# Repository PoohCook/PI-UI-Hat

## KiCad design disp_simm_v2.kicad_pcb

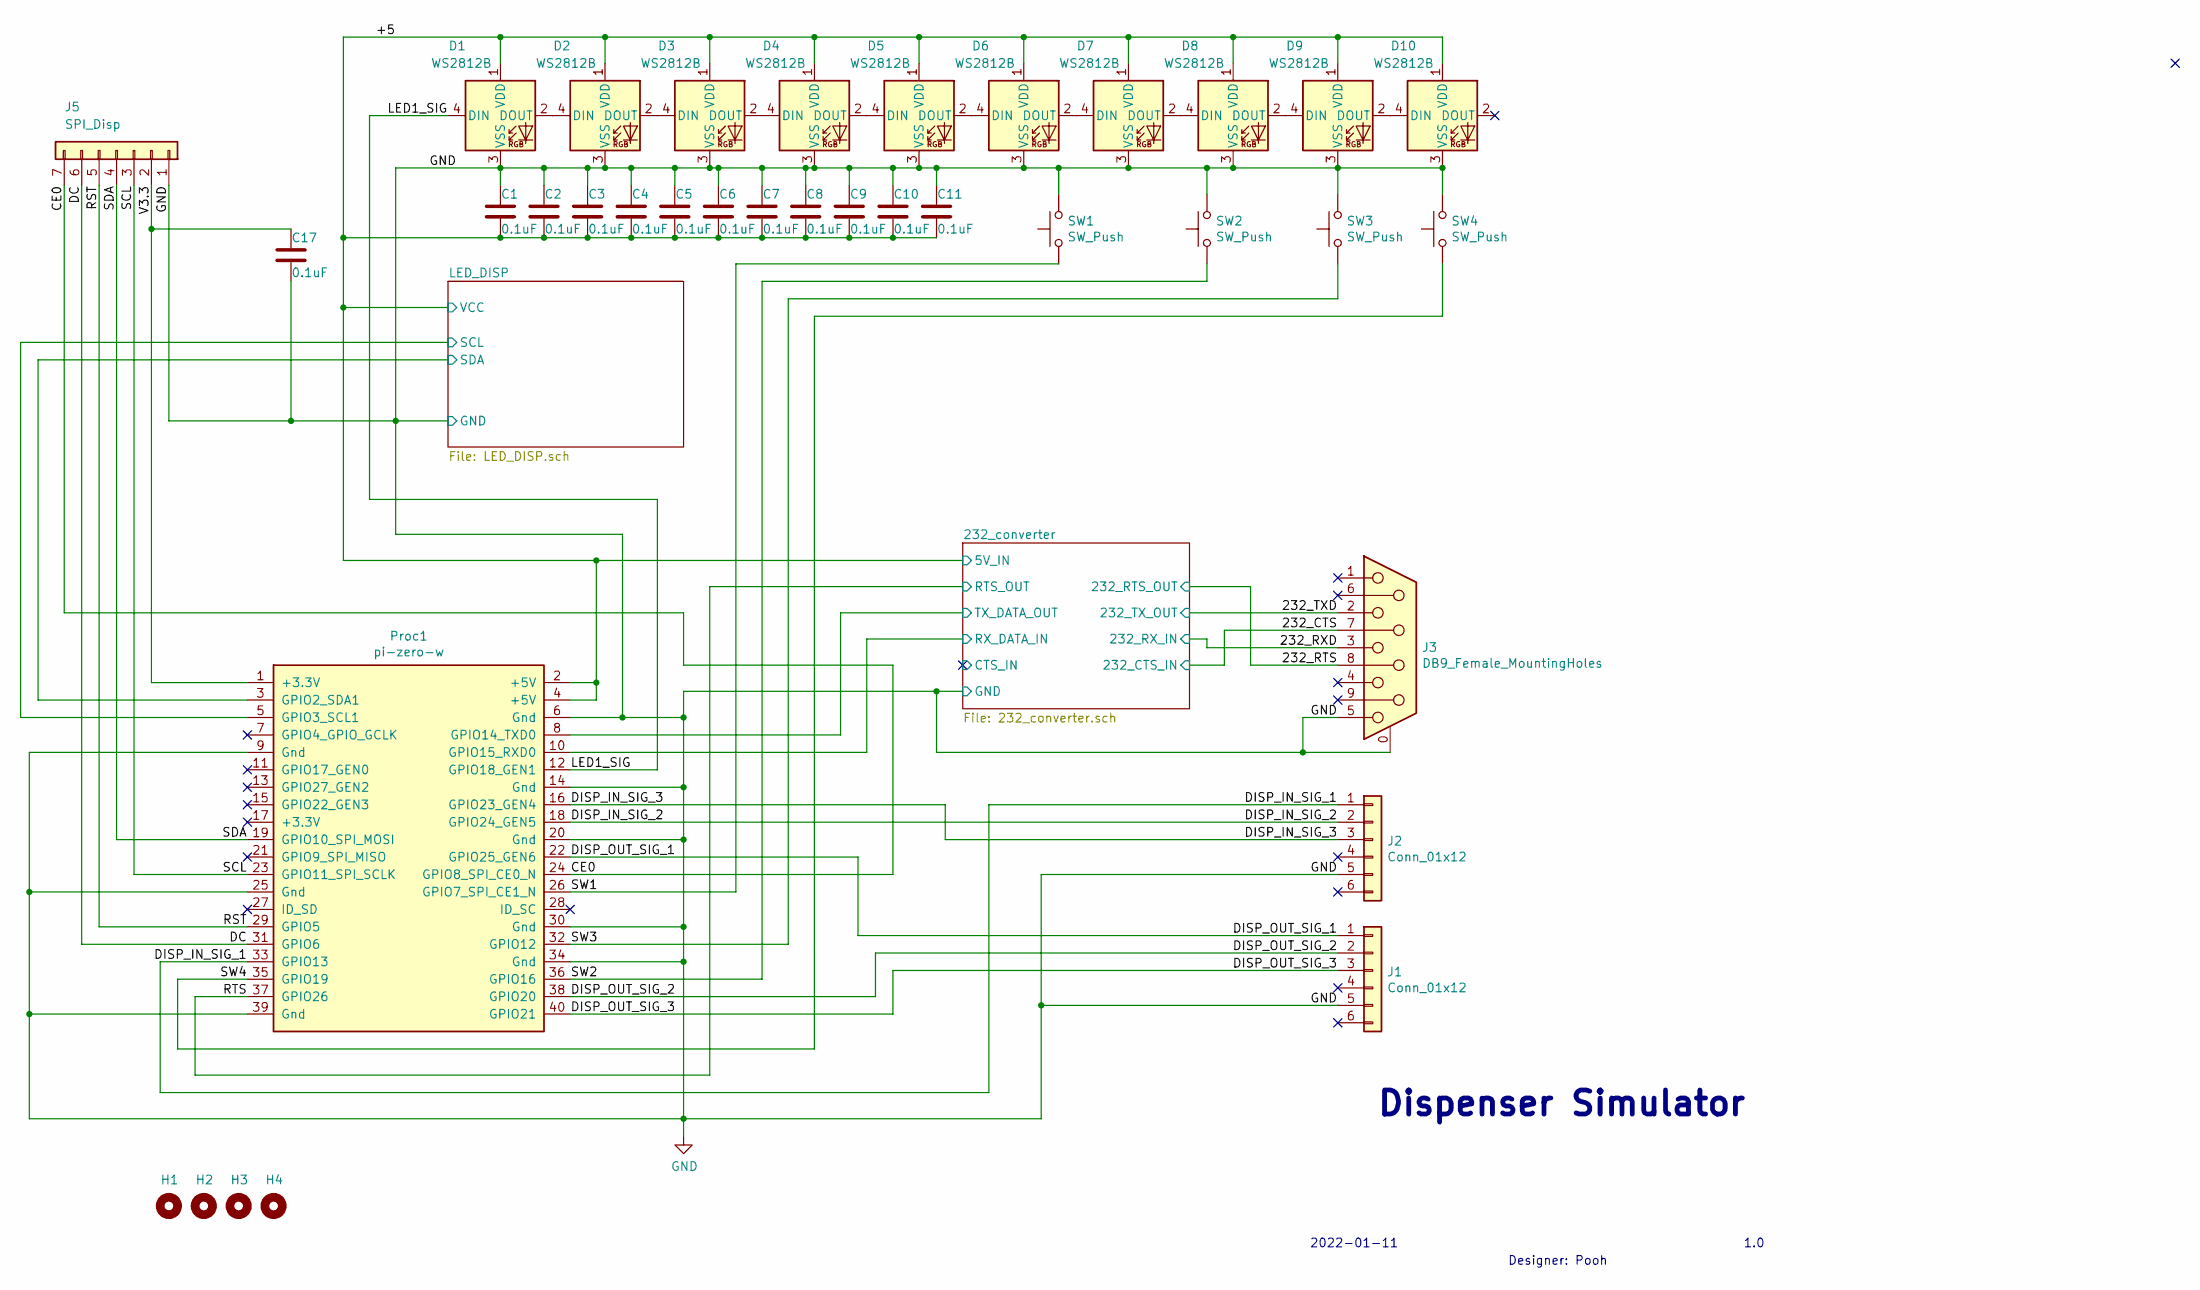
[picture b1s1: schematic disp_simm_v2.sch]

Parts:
C1, C2, C3, C4, C5, C6, C7, C8, C9, C10, C11, C17: 0.1uF; C_0805_2012Metric_Pad1.15x1.40mm_HandSolder; LCSC Part Number C49678
D1, D2, D3, D4, D5, D6, D7, D8, D9, D10: WS2812B; LED_WS2812B_PLCC4_5.0x5.0mm_P3.2mm; LCSC Part Number C2761795
H1, H2, H3, H4: MountingHole; MountingHole_2.5mm_Pad
J1, J2: Conn_01x12; JST-S06B-XASK-1
J3: DB9_Female_MountingHoles; DSUB-9_Female_Horizontal_P2.77x2.84mm_EdgePinOffset9.90mm_H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
J5: SPI_Disp; PinHeader_1x07_P2.54mm_Vertical
Proc1: pi-zero-w; pi-zero
SW1, SW2, SW3, SW4: SW_Push; SWA

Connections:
/232_CTS: J3.7; also elsewhere on the board
/232_RTS: J3.8; also elsewhere on the board
/232_RXD: J3.3; also elsewhere on the board
/232_TXD: J3.2; also elsewhere on the board
/232_converter/RX_DATA_IN: Proc1.10 (GPIO15_RXD0); also elsewhere on the board
/232_converter/TX_DATA_OUT: Proc1.8 (GPIO14_TXD0); also elsewhere on the board
/+5: C1.2, C2.2, C3.2, C4.2, C5.2, C6.2, C7.2, C8.2, C9.2, C10.2, C11.2, D1.1 (VDD), D2.1 (VDD), D3.1 (VDD), D4.1 (VDD), D5.1 (VDD), D6.1 (VDD), D7.1 (VDD), D8.1 (VDD), D9.1 (VDD), D10.1 (VDD), Proc1.2 (+5V), Proc1.4 (+5V); also elsewhere on the board
/CE0: J5.7, Proc1.24 (GPIO8_SPI_CE0_N)
/DC: J5.6, Proc1.31 (GPIO6)
/DISP_IN_SIG_1: J2.1, Proc1.33 (GPIO13)
/DISP_IN_SIG_2: J2.2, Proc1.18 (GPIO24_GEN5)
/DISP_IN_SIG_3: J2.3, Proc1.16 (GPIO23_GEN4)
/DISP_OUT_SIG_1: J1.1, Proc1.22 (GPIO25_GEN6)
/DISP_OUT_SIG_2: J1.2, Proc1.38 (GPIO20)
/DISP_OUT_SIG_3: J1.3, Proc1.40 (GPIO21)
/LED1_SIG: D1.4 (DIN), Proc1.12 (GPIO18_GEN1)
/LED_DISP/SCL: Proc1.5 (GPIO3_SCL1); also elsewhere on the board
/LED_DISP/SDA: Proc1.3 (GPIO2_SDA1); also elsewhere on the board
/RST: J5.5, Proc1.29 (GPIO5)
/RTS: Proc1.37 (GPIO26); also elsewhere on the board
/SCL: J5.3, Proc1.23 (GPIO11_SPI_SCLK)
/SDA: J5.4, Proc1.19 (GPIO10_SPI_MOSI)
/SW1: Proc1.26 (GPIO7_SPI_CE1_N), SW1.1
/SW2: Proc1.36 (GPIO16), SW2.1
/SW3: Proc1.32 (GPIO12), SW3.1
/SW4: Proc1.35 (GPIO19), SW4.1
/V3.3: C17.1, J5.2, Proc1.1 (+3.3V)
GND: C1.1, C2.1, C3.1, C4.1, C5.1, C6.1, C7.1, C8.1, C9.1, C10.1, C11.1, C17.2, D1.3 (VSS), D2.3 (VSS), D3.3 (VSS), D4.3 (VSS), D5.3 (VSS), D6.3 (VSS), D7.3 (VSS), D8.3 (VSS), D9.3 (VSS), D10.3 (VSS), J1.5, J2.5, J3.0 (PAD), J3.5, J5.1, Proc1.6 (Gnd), Proc1.9 (Gnd), Proc1.14 (Gnd), Proc1.20 (Gnd), Proc1.25 (Gnd), Proc1.30 (Gnd), Proc1.34 (Gnd), Proc1.39 (Gnd), SW1.2, SW2.2, SW3.2, SW4.2; also elsewhere on the board
unnamed: D1.2 (DOUT), D2.4 (DIN)
unnamed: D2.2 (DOUT), D3.4 (DIN)
unnamed: D3.2 (DOUT), D4.4 (DIN)
unnamed: D4.2 (DOUT), D5.4 (DIN)
unnamed: D5.2 (DOUT), D6.4 (DIN)
unnamed: D6.2 (DOUT), D7.4 (DIN)
unnamed: D7.2 (DOUT), D8.4 (DIN)
unnamed: D8.2 (DOUT), D9.4 (DIN)
unnamed: D9.2 (DOUT), D10.4 (DIN)

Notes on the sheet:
Dispenser Simulator
2022-01-11
1.0
Designer: Pooh

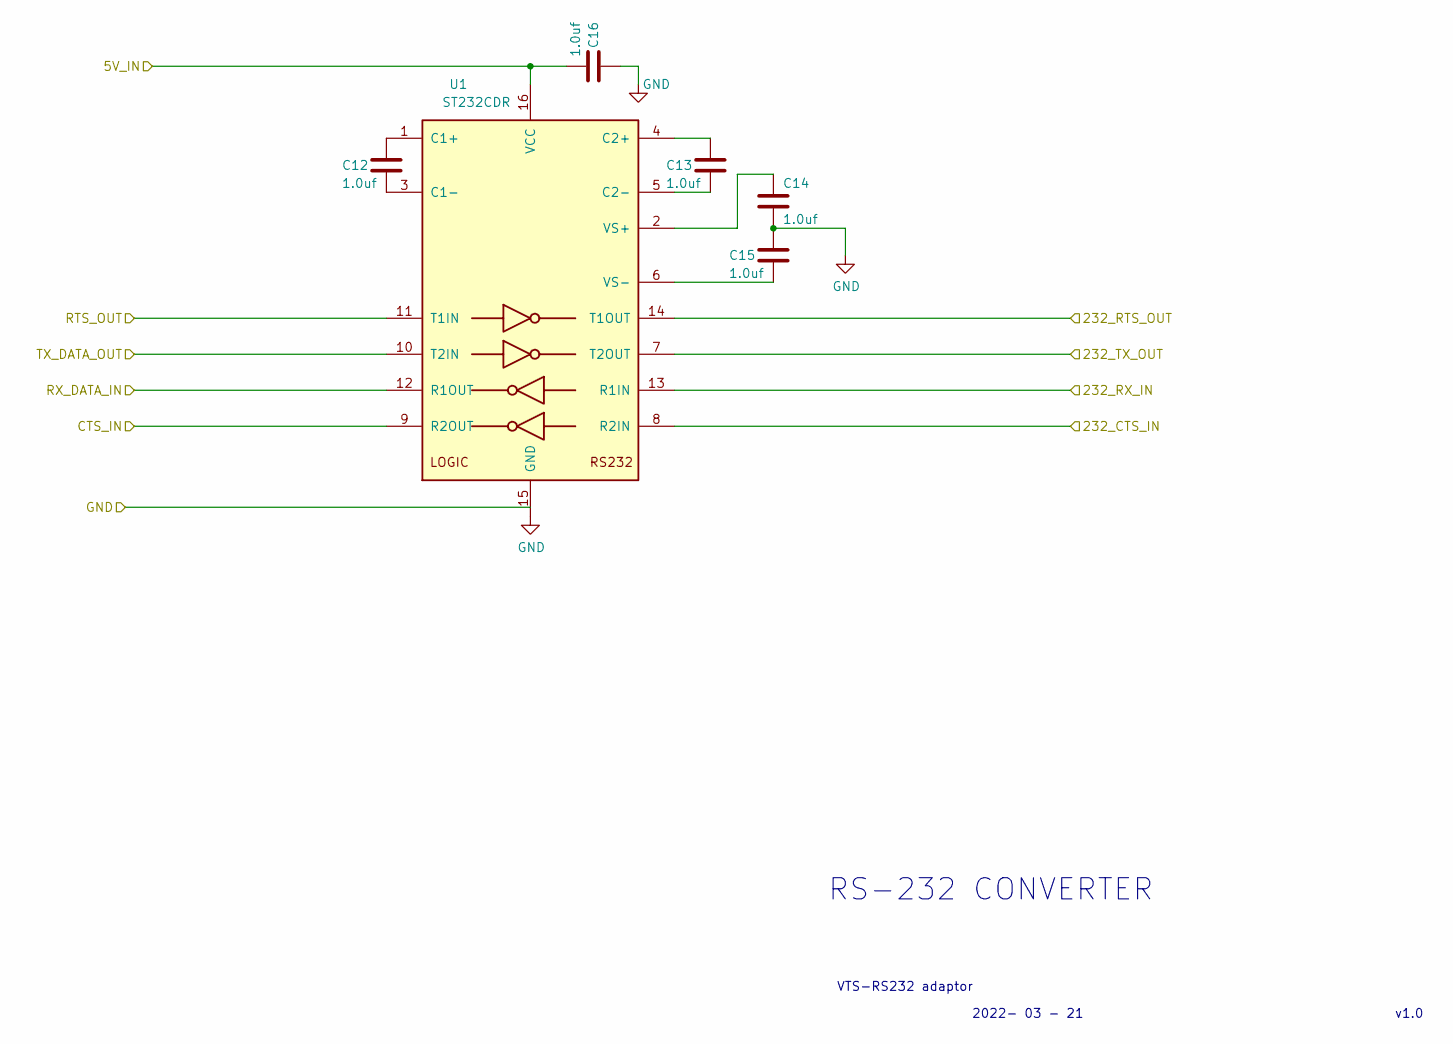
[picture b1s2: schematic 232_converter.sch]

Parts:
C12, C13, C14, C15, C16: 1.0uf; C_0805_2012Metric_Pad1.15x1.40mm_HandSolder; PartNum CL21B105KBFNNNE; LCSC Part Number C28323
U1: ST232CDR; SOIC-16_3.9x9.9mm_P1.27mm; PartNum ST232CDR; LCSC Part Number C6869

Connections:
/232_CTS: U1.8 (R2IN); also elsewhere on the board
/232_RTS: U1.14 (T1OUT); also elsewhere on the board
/232_RXD: U1.13 (R1IN); also elsewhere on the board
/232_TXD: U1.7 (T2OUT); also elsewhere on the board
/232_converter/CTS_IN: U1.9 (R2OUT)
/232_converter/RX_DATA_IN: U1.12 (R1OUT); also elsewhere on the board
/232_converter/TX_DATA_OUT: U1.10 (T2IN); also elsewhere on the board
/+5: C16.2, U1.16 (VCC); also elsewhere on the board
/RTS: U1.11 (T1IN); also elsewhere on the board
GND: C14.2, C15.1, C16.1, U1.15 (GND); also elsewhere on the board
unnamed: C12.1, U1.1 (C1+)
unnamed: C12.2, U1.3 (C1-)
unnamed: C13.1, U1.4 (C2+)
unnamed: C13.2, U1.5 (C2-)
unnamed: C14.1, U1.2 (VS+)
unnamed: C15.2, U1.6 (VS-)

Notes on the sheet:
RS-232 CONVERTER
VTS-RS232 adaptor
v1.0
2022- 03 - 21

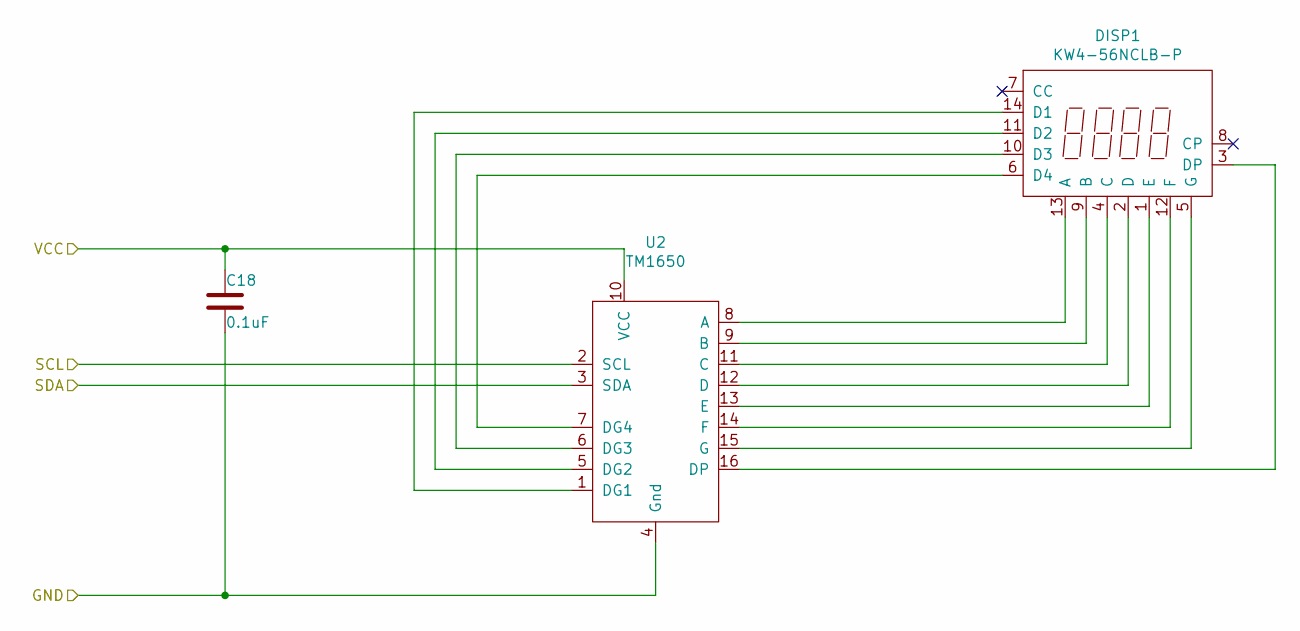
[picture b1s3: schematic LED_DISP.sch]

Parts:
C18: 0.1uF; C_0805_2012Metric_Pad1.15x1.40mm_HandSolder; LCSC Part Number C49678
DISP1: KW4-56NCLB-P; DIP-14_W15.24mm-Disp
U2: TM1650; SOP-16_4.55x10.3mm_P1.27mm; LCSC Part Number C44444

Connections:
/+5: C18.1, U2.10 (VCC); also elsewhere on the board
/LED_DISP/SCL: U2.2 (SCL); also elsewhere on the board
/LED_DISP/SDA: U2.3 (SDA); also elsewhere on the board
GND: C18.2, U2.4 (Gnd); also elsewhere on the board
unnamed: DISP1.1 (E), U2.13 (E)
unnamed: DISP1.2 (D), U2.12 (D)
unnamed: DISP1.3 (DP), U2.16 (DP)
unnamed: DISP1.4 (C), U2.11 (C)
unnamed: DISP1.5 (G), U2.15 (G)
unnamed: DISP1.6 (D4), U2.7 (DG4)
unnamed: DISP1.9 (B), U2.9 (B)
unnamed: DISP1.10 (D3), U2.6 (DG3)
unnamed: DISP1.11 (D2), U2.5 (DG2)
unnamed: DISP1.12 (F), U2.14 (F)
unnamed: DISP1.13 (A), U2.8 (A)
unnamed: DISP1.14 (D1), U2.1 (DG1)

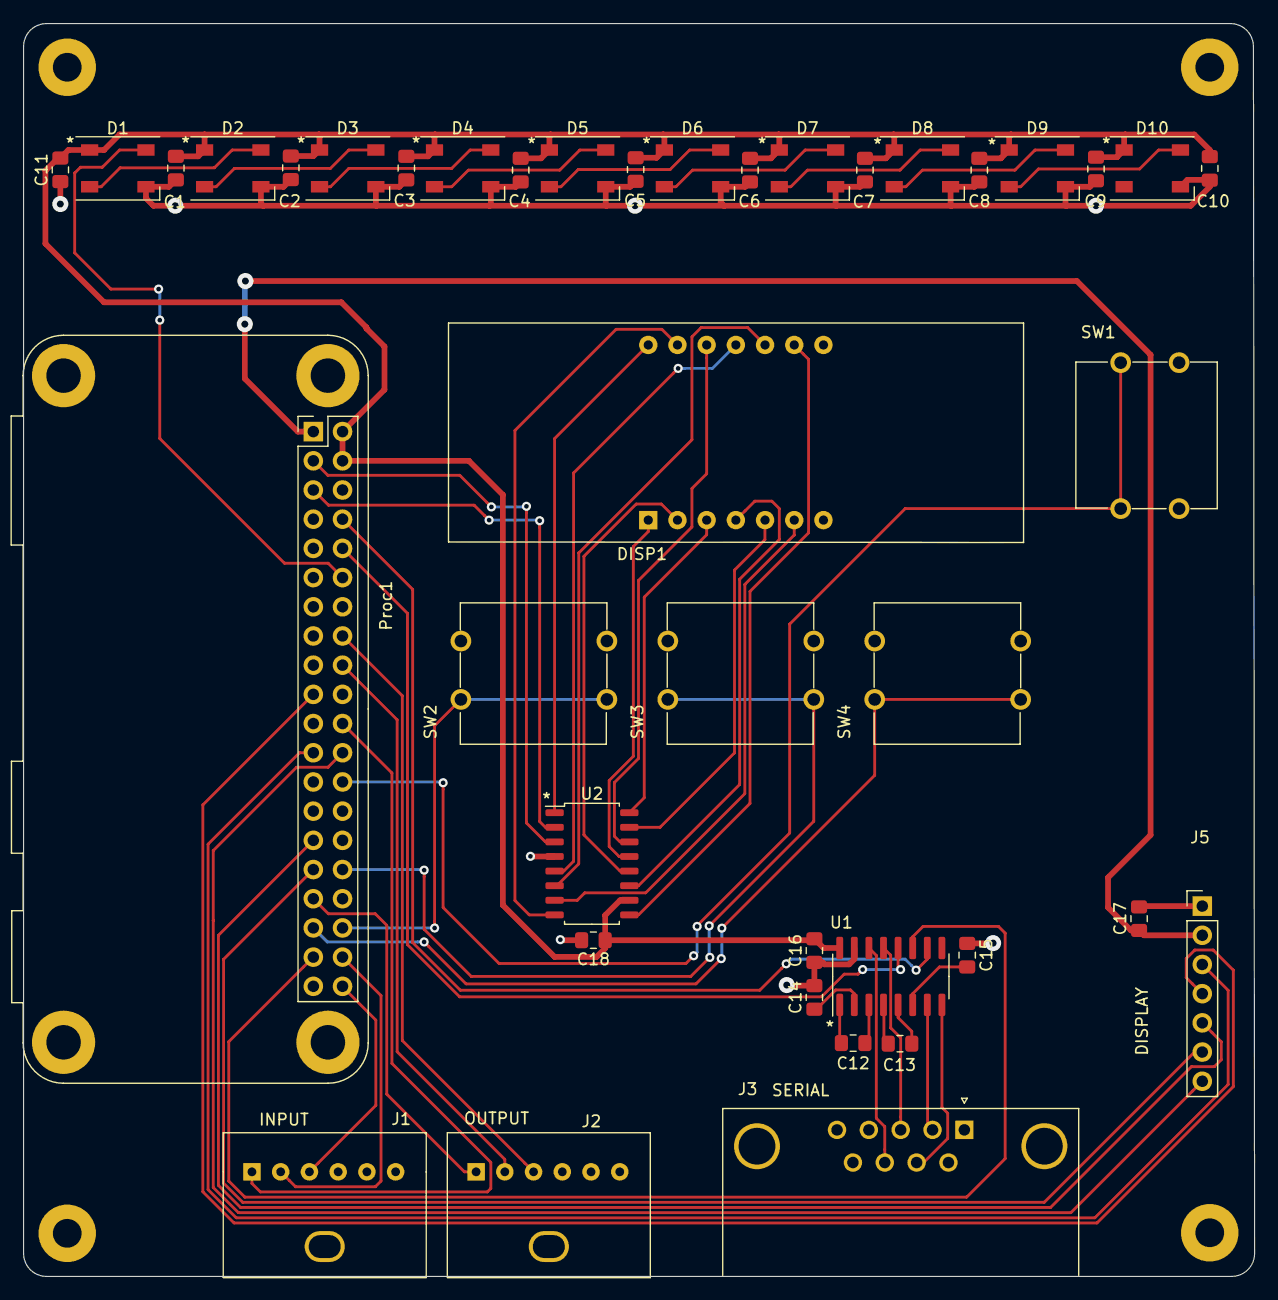
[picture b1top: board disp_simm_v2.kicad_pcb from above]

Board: 2 copper layers, 107.1 x 109.0 mm, 44 parts (0 on the bottom side), 55 nets.

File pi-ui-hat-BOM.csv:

Comment,Designator,Footprint, LCSC Part #
0.1uF,"C1, C2, C3, C4, C5, C6, C7, C8, C9, C10, C11, C17, C18",Capacitor_SMD:C_0805_2012Metric_Pad1.15x1.40mm_HandSolder,C49678
1.0uf,"C12, C13, C14, C15, C16",Capacitor_SMD:C_0805_2012Metric_Pad1.15x1.40mm_HandSolder,C28323
WS2812B,"D1, D2, D3, D4, D5, D6, D7, D8, D9, D10",LED_SMD:LED_WS2812B_PLCC4_5.0x5.0mm_P3.2mm,C2761795
ST232CDR,U1,Package_SO:SOIC-16_3.9x9.9mm_P1.27mm,C6869
TM1650,U2,Package_SO:SOP-16_4.55x10.3mm_P1.27mm,C44444

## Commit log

2022-03-31 initial put
